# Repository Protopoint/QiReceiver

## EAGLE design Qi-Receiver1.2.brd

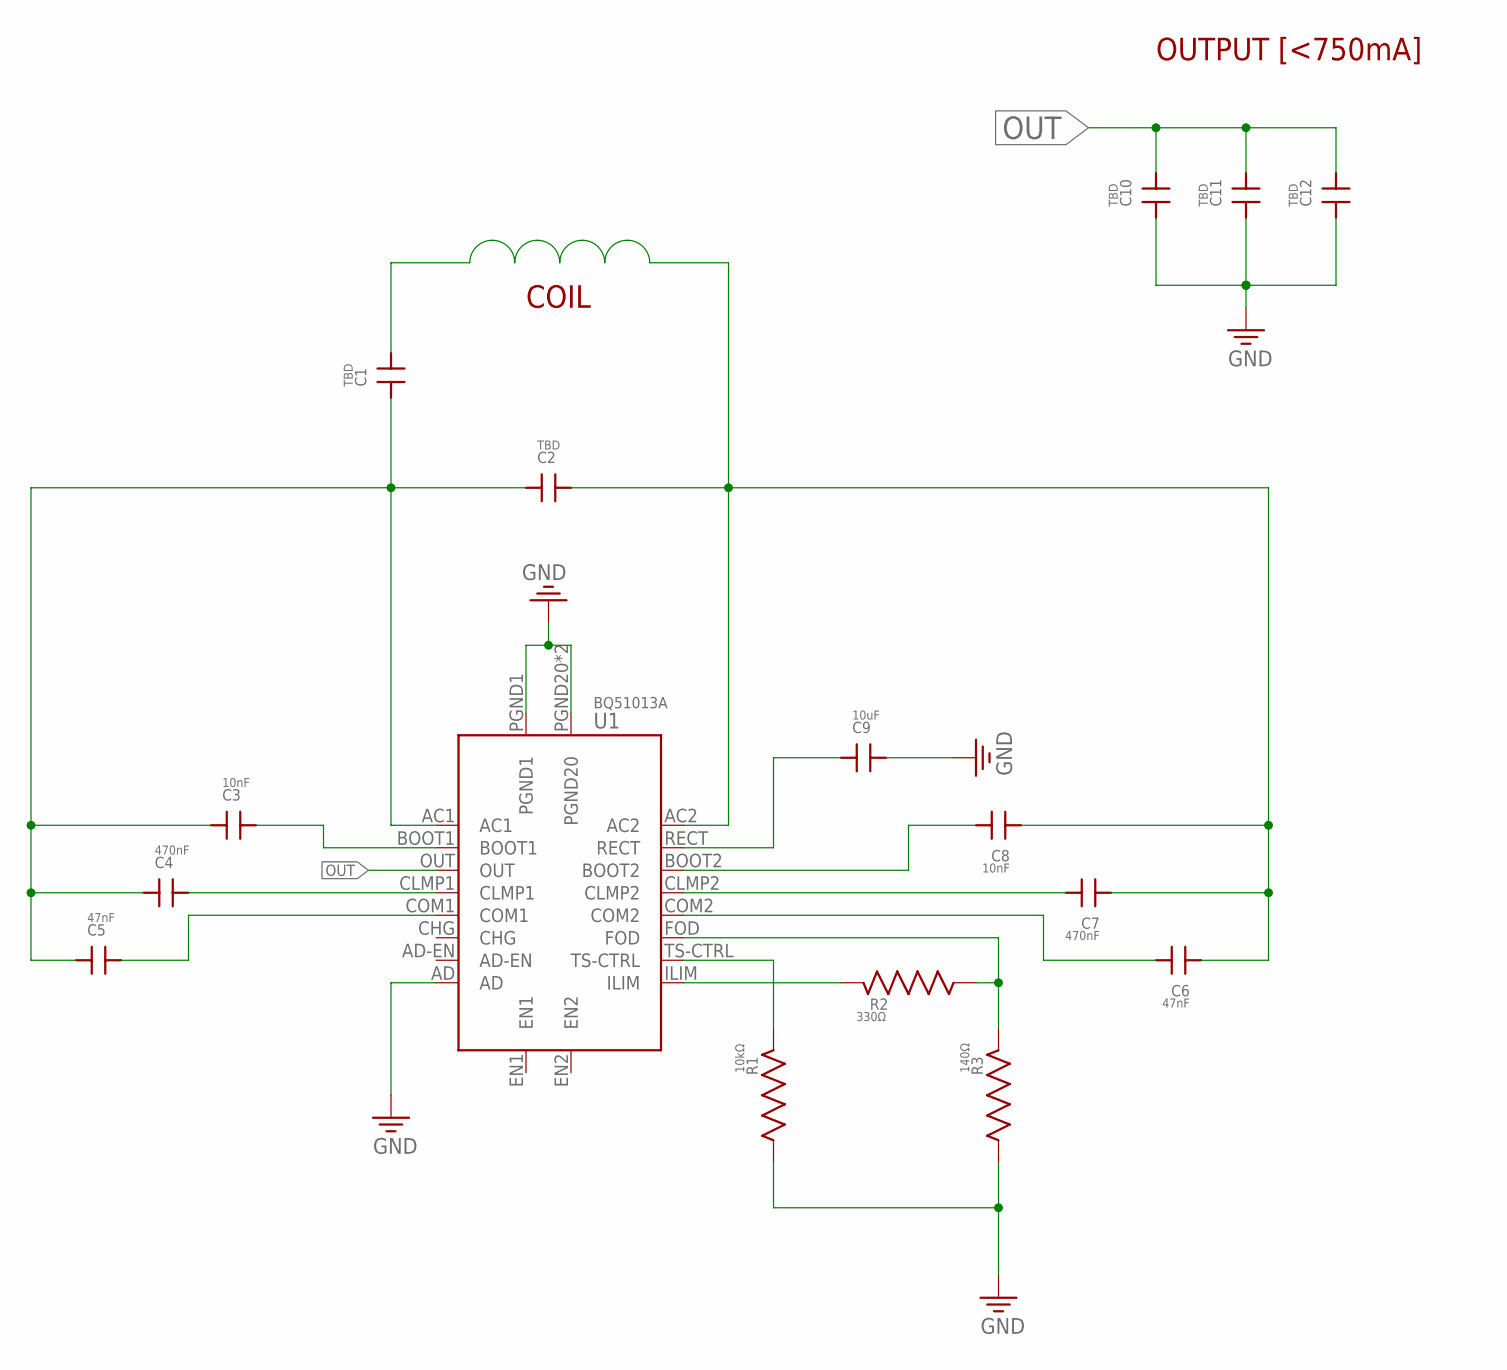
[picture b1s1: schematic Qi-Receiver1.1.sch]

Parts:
C1, C2, C10, C11, C12: TBD; 0402-SMT
C3, C8: 10nF; 0402-SMT
C4, C7: 470nF; 0402-SMT
C5, C6: 47nF; 0402-SMT
C9: 10uF; 0402-SMT
R1: 10kΩ; 0402-SMT
R2: 330Ω; 0402-SMT
R3: 140Ω; 0402-SMT
U1: BQ51013A

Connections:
AC1: C1.P$1, C2.P$1, C3.P$1, C4.P$1, C5.P$1, U1.AC1
AC2: C1.P$2, C2.P$2, C6.P$1, C7.P$1, C8.P$1, U1.AC2
BOOT1: C3.P$2, U1.BOOT1
BOOT2: C8.P$2, U1.BOOT2
CHG: U1.CHG; also elsewhere on the board
CLMP1: C4.P$2, U1.CLMP1
CLMP2: C7.P$2, U1.CLMP2
COM1: C5.P$2, U1.COM1
COM2: C6.P$2, U1.COM2
FOD: R2.P$1, R3.P$2, U1.FOD
GND: C9.P$2, C10.P$1, C11.P$1, C12.P$1, R1.P$1, R3.P$1, U1.AD, U1.PGND1, U1.PGND20, U1.THERM (PGND20)
ILIM: R2.P$2, U1.ILIM
unnamed: R1.P$2, U1.TS-CTRL
OUT: C10.P$2, C11.P$2, C12.P$2, U1.OUT; also elsewhere on the board
RECT: C9.P$1, U1.RECT

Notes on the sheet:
COIL
OUTPUT [<750mA]

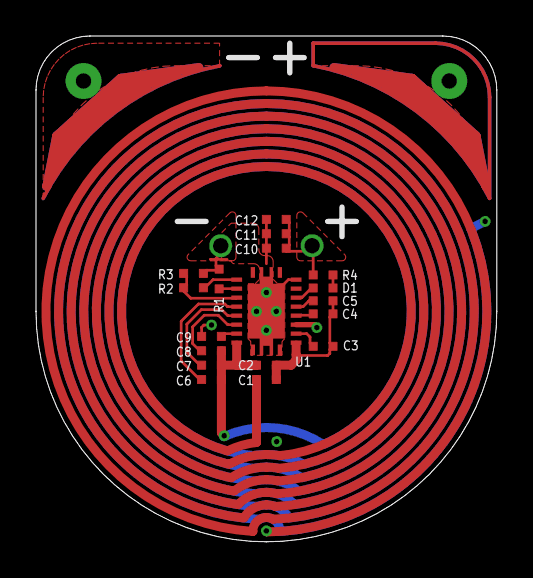
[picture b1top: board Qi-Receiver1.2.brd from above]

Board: 4 copper layers, 25.6 x 28.1 mm, 18 parts (0 on the bottom side), 16 nets.

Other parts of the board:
D1: 0402-LED; 0402-SMT
R4: 1000Ω; 0402-SMT

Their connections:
CHG: D1.P$2; also elsewhere on the board
unnamed: D1.P$1, R4.P$1
OUT: R4.P$2; also elsewhere on the board

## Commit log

2023-11-28 Initial Commit
    All design files and outputs for v1 revision 2 of the Qi Receiver.
    This commit is being made on behalf of the Cory Lord / Protopoint
